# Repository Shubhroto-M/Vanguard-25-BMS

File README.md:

# 🐉 VANGUARD 25: Industrial-Grade 5S Battery Management System

> **Vanguard 25** is an open-source, high-current (20A) Battery Management System designed with strict, aerospace-style redundant safety architectures. It is built to handle massive current dumps while protecting lithium-ion chemistry from catastrophic failure modes.

*(Insert your best 3D Render of the top and bottom of the board here)*

## ⚡ Core Specifications
* **Architecture:** 5S (Configurable down to 3S/4S via hardware solder jumpers).
* **Operating Voltage:** 21V Max.
* **Current Capacity:** 25A Continuous / 45A Peak Over-current.
* **Balancing:** 150mA active hardware balancing per cell.
* **PCB Specs:** 2-Layer, standard 1oz/2oz copper, designed for Matte Black Solder Mask with ENIG (Gold) plating.

## 🛡️ Dual-Tier Safety Architecture
Unlike standard hobbyist BMS boards that rely on a single point of failure, Vanguard 25 implements a strictly hardware-based, dual-redundant safety net. **There is zero firmware to crash.**

1. **Primary Logic (BM3451):** Handles standard cell balancing, over-charge (OVP), over-discharge (UVP), and over-current protection.
2. **Redundant Failsafe (BQ771807):** The "Paranoia Chip." Runs on a completely independent internal voltage reference. If a cell hits a critical **4.5V hard cutoff**, it bypasses the main logic entirely.
3. **Hardware Kill Switch (Dexerials SKF-2045):** If the BQ771807 trips, it fires a voltage into the heater element of this chemical fuse, physically and permanently severing the main power line to prevent thermal runaway.

## 📐 Layout & Routing Strategy
* **Total Signal Isolation:** Massive, high-current copper polygons are restricted to the outer edges of the board. The sensitive analog measurement lines and logic ICs are grouped in a protected central island to prevent EMI and switching noise interference.
* **Thermal Management:** The parallel MOSFET bridge features aggressive thermal via stitching, allowing the internal and bottom copper planes to act as massive passive heatsinks during 25A continuous loads.
* **DRC Cleared:** 0 Errors, 0 Warnings under strict clearance constraints.

## 📁 Repository Contents
* `/KiCad_Project` - Full schematic and PCB layout files.
* `/Gerbers` - Production-ready manufacturing files.
* `/3D_Models` - STEP files for mechanical enclosure integration.

## ⚠️ DANGER & DISCLAIMER
**Lithium-Ion batteries contain massive amounts of energy and can cause fires, explosions, and severe injury if mishandled.**
This repository is provided as an open-source portfolio project and educational reference. It has not been tested by UL, CE, or any other regulatory body. If you choose to fabricate this board, populate the components, and connect it to live lithium cells, you do so entirely at your own risk. The designer takes absolutely zero responsibility for any damage to property, equipment, or persons. 

---
*Designed in Bengaluru.*

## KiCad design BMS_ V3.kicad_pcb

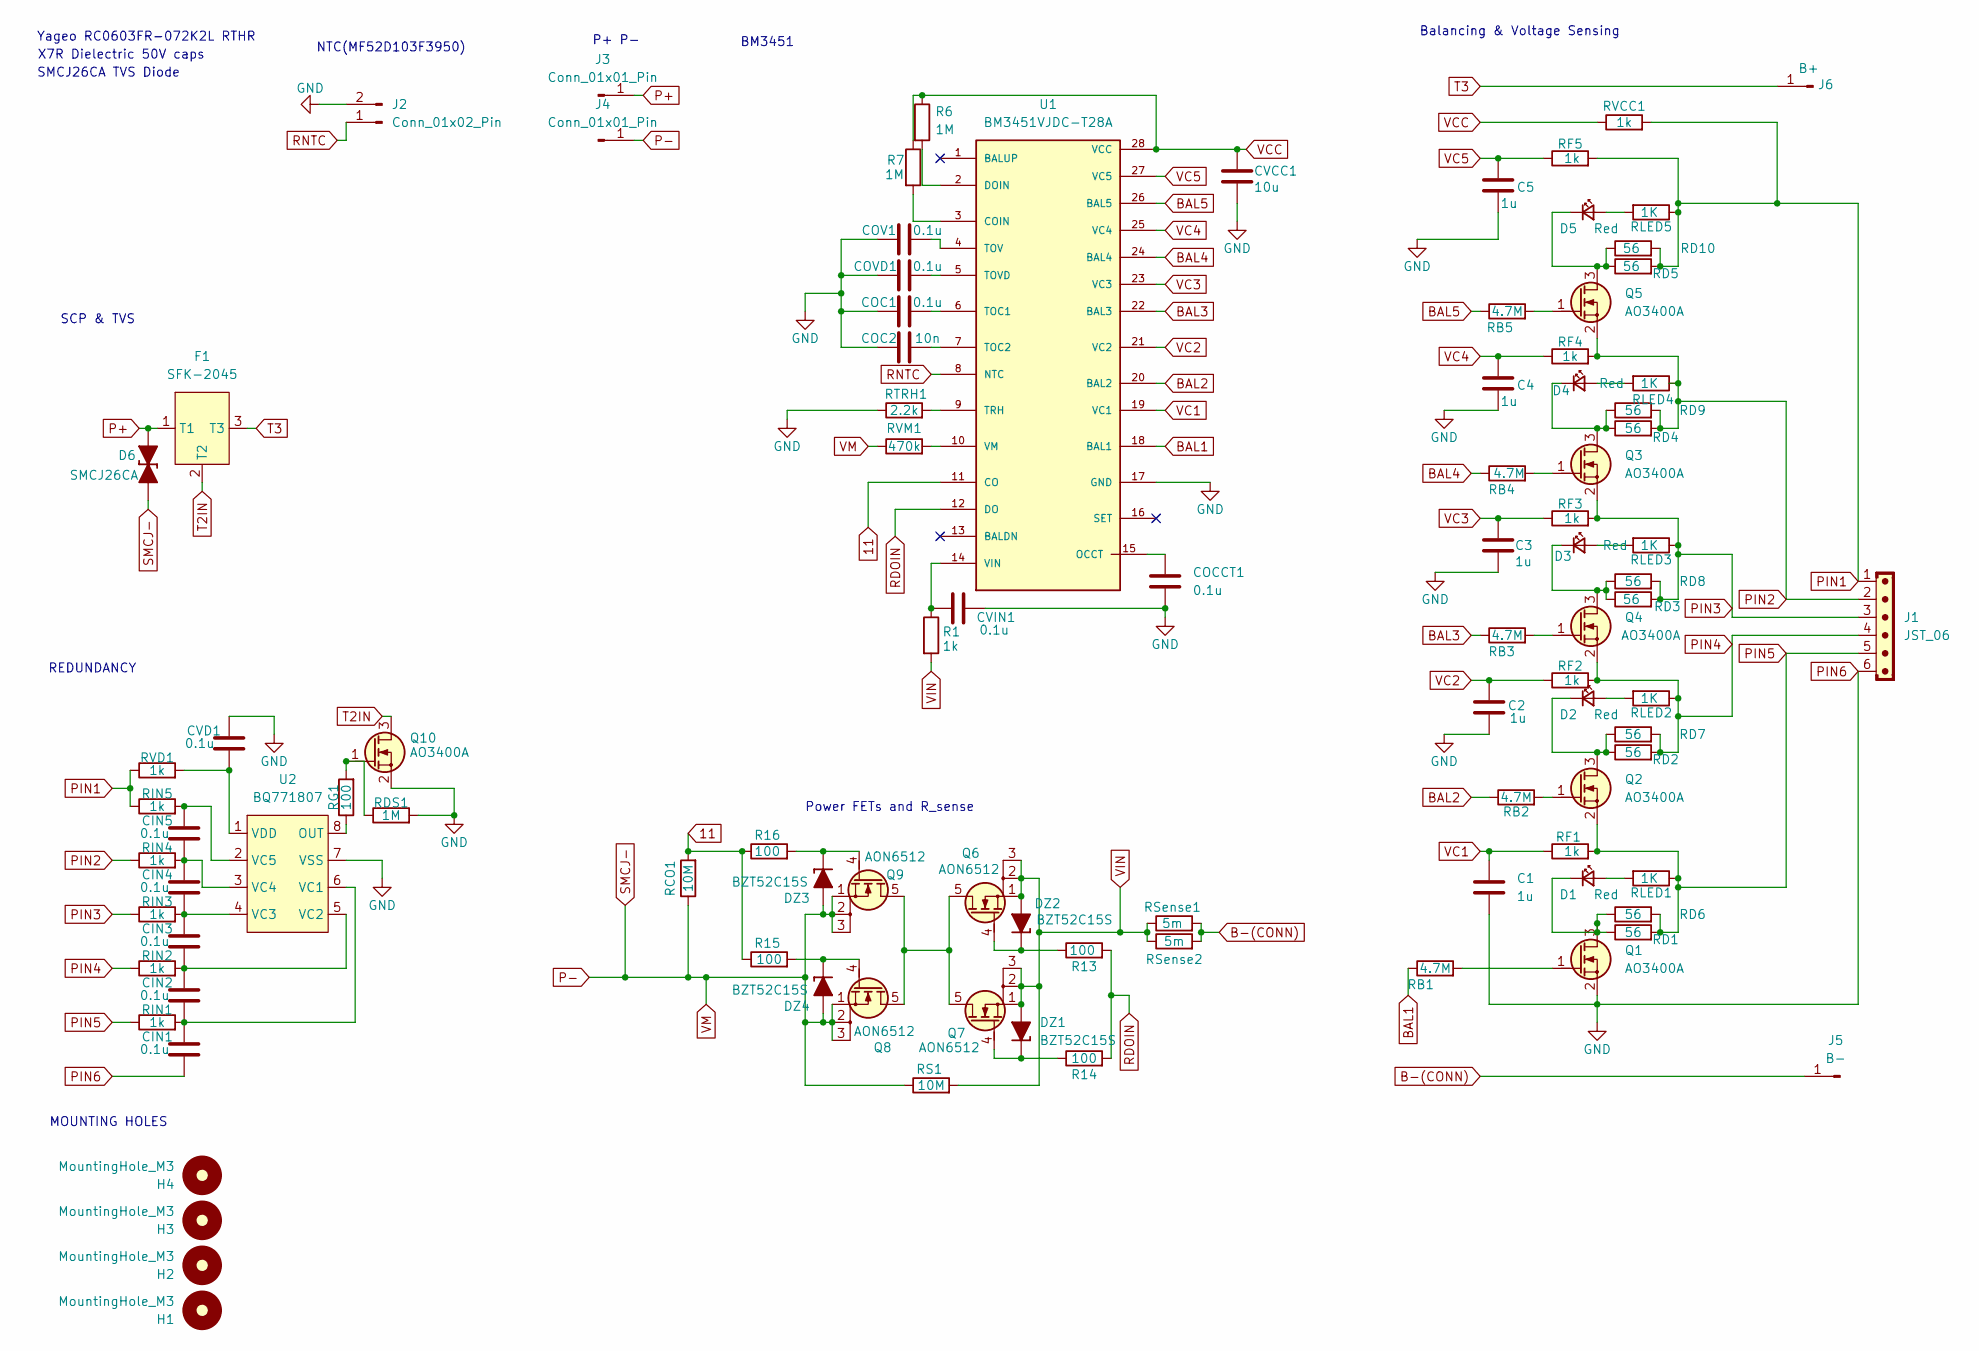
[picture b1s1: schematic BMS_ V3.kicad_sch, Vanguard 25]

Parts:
C1, C2, C3, C4, C5: 1u; C_0603_1608Metric
CIN1, CIN2, CIN3, CIN4, CIN5: 0.1u; C_0603_1608Metric
COC1: 0.1u; C_0603_1608Metric
COC2: 10n; C_0603_1608Metric
COCCT1: 0.1u; C_0603_1608Metric
COV1: 0.1u; C_0603_1608Metric
COVD1: 0.1u; C_0603_1608Metric
CVCC1: 10u; C_0603_1608Metric
CVD1: 0.1u; C_0603_1608Metric
CVIN1: 0.1u; C_0603_1608Metric
D1, D2, D3, D4, D5: Red; LED_0603_1608Metric_Red
D6: SMCJ26CA; D_SMC_TVS
DZ1, DZ2, DZ3, DZ4: BZT52C15S; D_SOD-323
F1: SFK-2045; SFK-2450
H1, H2, H3, H4: MountingHole_M3; MountingHole_3.2mm_M3
J1: JST_06; JST_EH_B6B-EH-A_1x06_P2.50mm_Vertical
J2: Conn_01x02_Pin; JST_EH_B2B-EH-A_1x02_P2.50mm_Vertical
J3, J4: Conn_01x01_Pin; TestPoint_Pad_4.0x4.0mm
J5: B-; TestPoint_Pad_4.0x4.0mm
J6: B+; TestPoint_Pad_4.0x4.0mm
Q1, Q2, Q3, Q4, Q5, Q10: AO3400A; SOT-23
Q6, Q7, Q8, Q9: AON6512; Infineon_PG-TDSON-8
R1: 1k; R_0603_1608Metric
R6, R7: 1M; R_0603_1608Metric
R13, R14, R15, R16: 100; R_0603_1608Metric
RB1, RB2, RB3, RB4, RB5: 4.7M; R_0603_1608Metric
RCO1: 10M; R_0603_1608Metric
RD1, RD2, RD3, RD4, RD5, RD6, RD7, RD8, RD9, RD10: 56; R_2010_5025Metric
RDS1: 1M; R_0603_1608Metric
RF1, RF2, RF3, RF4, RF5: 1k; R_0603_1608Metric
RG1: 100; R_0603_1608Metric
RIN1, RIN2, RIN3, RIN4, RIN5: 1k; R_0603_1608Metric
RLED1, RLED2, RLED3, RLED4, RLED5: 1K; R_0603_1608Metric
RS1: 10M; R_0603_1608Metric
RSense1, RSense2: 5m; R_2512_6332Metric
RTRH1: 2.2k; R_0603_1608Metric
RVCC1: 1k; R_0603_1608Metric
RVD1: 1k; R_0603_1608Metric
RVM1: 470k; R_0603_1608Metric
U1: BM3451VJDC-T28A; TSSOP-28_4.4x9.7mm_P0.65mm; PARTREV A/1
U2: BQ771807; VSSOP-8_3x3mm_P0.65mm

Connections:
11: R15.1, R16.1, RCO1.2, U1.11 (CO)
B-(CONN): J5.1, RSense1.2, RSense2.2
BAL1: RB1.1, U1.18 (BAL1)
BAL2: RB2.1, U1.20 (BAL2)
BAL3: RB3.1, U1.22 (BAL3)
BAL4: RB4.1, U1.24 (BAL4)
BAL5: RB5.1, U1.26 (BAL5)
unnamed: D1.2 (A), RLED1.2
unnamed: D1.1 (K), Q1.3 (D), RD1.1, RD6.1
unnamed: D2.2 (A), RLED2.2
unnamed: D2.1 (K), Q2.3 (D), RD2.1, RD7.1
unnamed: D3.2 (A), RLED3.2
unnamed: D3.1 (K), Q4.3 (D), RD3.1, RD8.1
unnamed: D4.2 (A), RLED4.2
unnamed: D4.1 (K), Q3.3 (D), RD4.1, RD9.1
unnamed: D5.2 (A), RLED5.2
unnamed: D5.1 (K), Q5.3 (D), RD5.1, RD10.1
unnamed: DZ1.1 (K), Q7.4 (G), R14.1
unnamed: DZ2.1 (K), Q6.4 (G), R13.1
unnamed: DZ3.1 (K), Q9.4 (G), R16.2
unnamed: DZ4.1 (K), Q8.4 (G), R15.2
unnamed: Q1.1 (G), RB1.2
unnamed: Q2.1 (G), RB2.2
unnamed: Q3.1 (G), RB4.2
unnamed: Q4.1 (G), RB3.2
unnamed: Q5.1 (G), RB5.2
unnamed: Q6.5 (D), Q7.5 (D), Q8.5 (D), Q9.5 (D)
unnamed: Q10.1 (G), RDS1.1, RG1.2
unnamed: R7.2, U1.3 (COIN)
unnamed: R6.2, U1.2 (DOIN)
unnamed: COCCT1.1, U1.15 (OCCT)
unnamed: COC1.2, U1.6 (TOC1)
unnamed: COC2.2, U1.7 (TOC2)
unnamed: COV1.2, U1.4 (TOV)
unnamed: COVD1.2, U1.5 (TOVD)
unnamed: RTRH1.2, U1.9 (TRH)
unnamed: CVIN1.1, R1.1, U1.14 (VIN)
unnamed: RVM1.2, U1.10 (VM)
unnamed: RG1.1, U2.8 (OUT)
unnamed: CIN1.1, CIN2.2, RIN1.2, U2.6 (VC1)
unnamed: CIN2.1, CIN3.2, RIN2.2, U2.5 (VC2)
unnamed: CIN3.1, CIN4.2, RIN3.2, U2.4 (VC3)
unnamed: CIN4.1, CIN5.2, RIN4.2, U2.3 (VC4)
unnamed: CIN5.1, RIN5.2, U2.2 (VC5)
unnamed: CVD1.2, RVD1.2, U2.1 (VDD)
P+: D6.2 (A), F1.1 (T1), J3.1
P-: D6.1 (K), DZ3.2 (A), DZ4.2 (A), J4.1, Q8.1 (S), Q8.2 (S), Q8.3 (S), Q9.1 (S), Q9.2 (S), Q9.3 (S), RCO1.1, RS1.1, RVM1.1
PIN1: J1.1, RD5.2, RD10.2, RF5.2, RIN5.1, RLED5.1, RVCC1.2, RVD1.1
PIN2: J1.2, Q5.2 (S), RD4.2, RD9.2, RF4.2, RIN4.1, RLED4.1
PIN3: J1.3, Q3.2 (S), RD3.2, RD8.2, RF3.2, RIN3.1, RLED3.1
PIN4: J1.4, Q4.2 (S), RD2.2, RD7.2, RF2.2, RIN2.1, RLED2.1
PIN5: J1.5, Q2.2 (S), RD1.2, RD6.2, RF1.2, RIN1.1, RLED1.1
PIN6: C1.2, C2.2, C3.2, C4.2, C5.2, CIN1.2, COC1.1, COC2.1, COCCT1.2, COV1.1, COVD1.1, CVCC1.2, CVD1.1, CVIN1.2, J1.6, J2.2, Q1.2 (S), Q10.2 (S), RDS1.2, RTRH1.1, U1.17 (GND), U2.7 (VSS)
RDOIN: R13.2, R14.2, U1.12 (DO)
RNTC: J2.1, U1.8 (NTC)
T2IN: F1.2 (T2), Q10.3 (D)
T3: F1.3 (T3), J6.1
VC1: C1.1, RF1.1, U1.19 (VC1)
VC2: C2.1, RF2.1, U1.21 (VC2)
VC3: C3.1, RF3.1, U1.23 (VC3)
VC4: C4.1, RF4.1, U1.25 (VC4)
VC5: C5.1, RF5.1, U1.27 (VC5)
VCC: CVCC1.1, R6.1, R7.1, RVCC1.1, U1.28 (VCC)
VIN: DZ1.2 (A), DZ2.2 (A), Q6.1 (S), Q6.2 (S), Q6.3 (S), Q7.1 (S), Q7.2 (S), Q7.3 (S), R1.2, RS1.2, RSense1.1, RSense2.1

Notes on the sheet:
MOUNTING HOLES
Power FETs and R_sense
Balancing & Voltage Sensing
P+ P-
SMCJ26CA TVS Diode
X7R Dielectric 50V caps
SCP & TVS
NTC(MF52D103F3950)
BM3451
Yageo RC0603FR-072K2L RTHR
REDUNDANCY

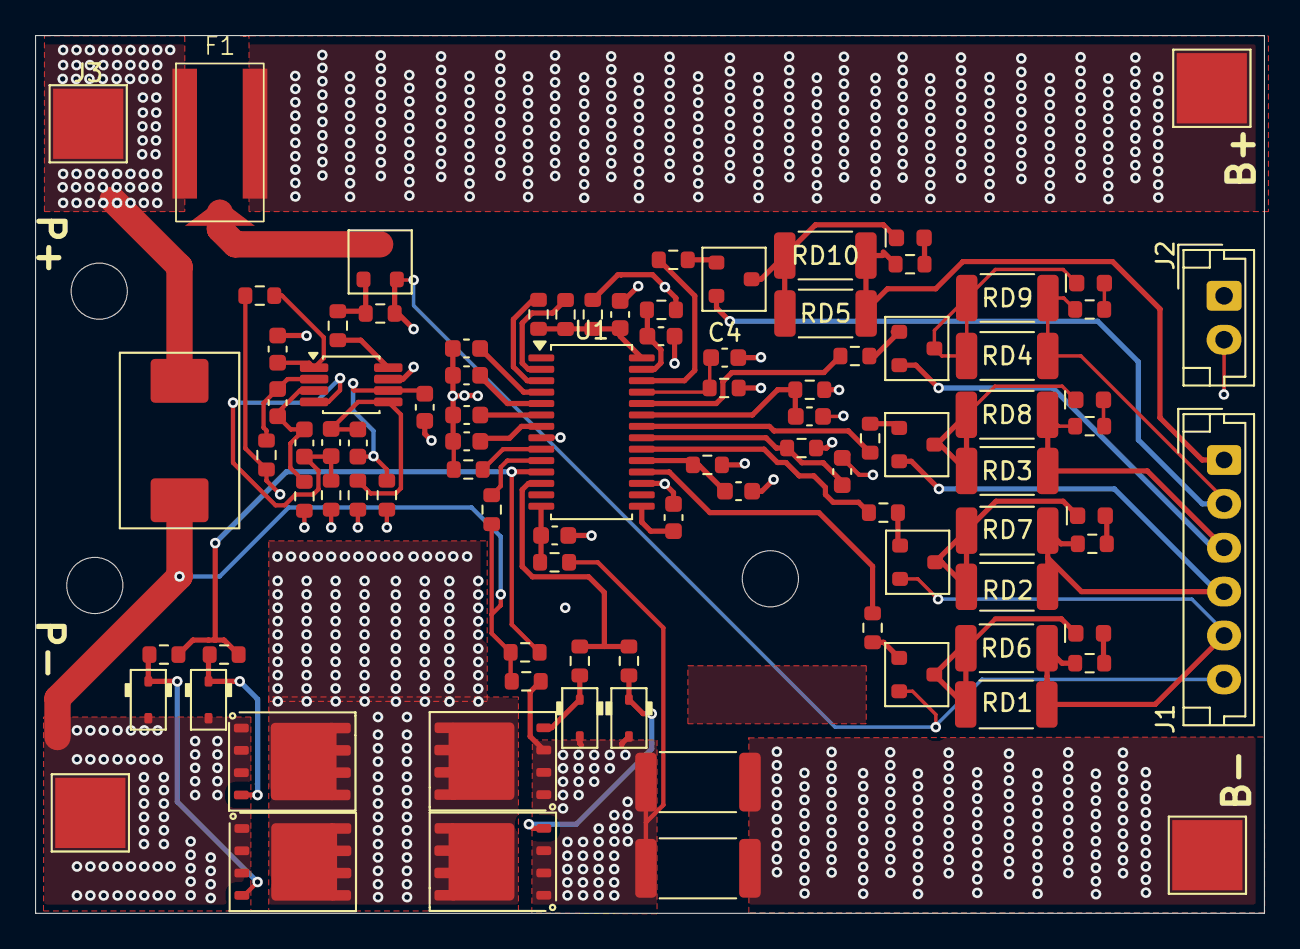
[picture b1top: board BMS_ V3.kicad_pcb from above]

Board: 4 copper layers, 70.0 x 50.0 mm, 97 parts (0 on the bottom side), 64 nets.

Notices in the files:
README.md:
License: MIT
